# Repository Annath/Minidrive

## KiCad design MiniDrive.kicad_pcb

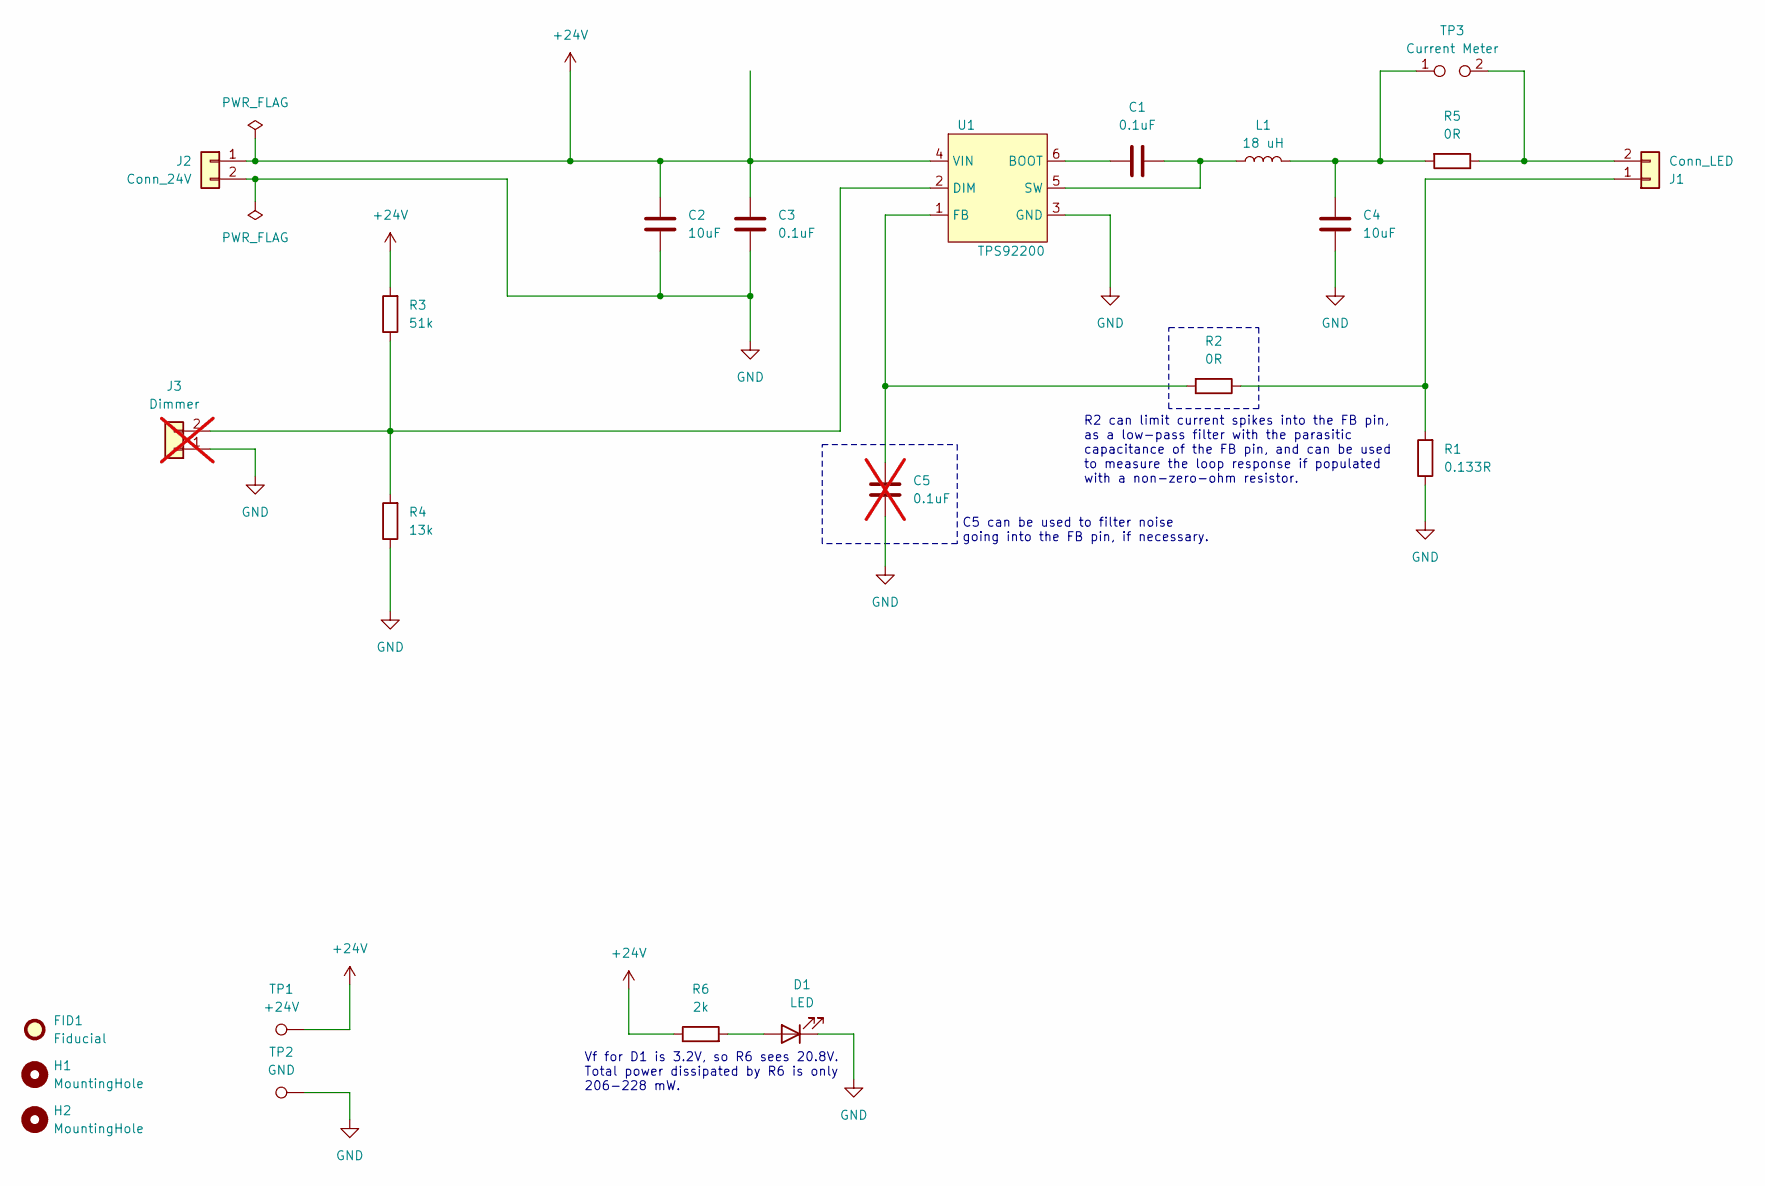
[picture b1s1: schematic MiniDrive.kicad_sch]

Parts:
C1, C3: 0.1uF; C_1210_3225Metric
C2, C4: 10uF; C_1206_3216Metric
C5: 0.1uF; C_0402_1005Metric; not fitted
D1: LED; LED_0603_1608Metric
FID1: Fiducial; Fiducial_0.5mm_Mask1mm
H1, H2: MountingHole; MountingHole_3.2mm_M3
J1: Conn_LED; Molex_Micro-Fit_3.0_43650-0200_1x02_P3.00mm_Horizontal
J2: Conn_24V; Molex_Micro-Fit_3.0_43650-0200_1x02_P3.00mm_Horizontal
J3: Dimmer; JST_PH_B2B-PH-K_1x02_P2.00mm_Vertical; not fitted
L1: 18 uH; L_Wurth_WE-LQS-8040
R1: 0.133R; R_1206_3216Metric
R2, R5: 0R; R_1206_3216Metric
R3: 51k; R_1206_3216Metric
R4: 13k; R_1206_3216Metric
R6: 2k; R_0805_2012Metric
TP1: +24V; TestPoint_THTPad_D1.5mm_Drill0.7mm
TP2: GND; TestPoint_THTPad_D1.5mm_Drill0.7mm
TP3: Current Meter; TestPoint_2Pads_Pitch2.54mm_Drill0.8mm
U1: TPS92200; SOT-23-6

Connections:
+24V: C2.1, C3.1, J2.1, R3.2, R6.1, TP1.1, U1.4 (VIN)
GND: C2.2, C3.2, C4.2, C5.2, D1.1 (K), J2.2, J3.1, R1.1, R4.1, TP2.1, U1.3 (GND)
unnamed: C4.1, L1.2, R5.2, TP3.1
unnamed: D1.2 (A), R6.2
unnamed: J1.1, R1.2, R2.1
unnamed: J1.2, R5.1, TP3.2
unnamed: J3.2, R3.1, R4.2, U1.2 (DIM)
unnamed: C1.2, U1.6 (BOOT)
unnamed: C5.1, R2.2, U1.1 (FB)
unnamed: C1.1, L1.1, U1.5 (SW)

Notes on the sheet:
Vf for D1 is 3.2V, so R6 sees 20.8V. Total power dissipated by R6 is only 206-228 mW.
R2 can limit current spikes into the FB pin, as a low-pass filter with the parasitic capacitance of the FB pin, and can be used to measure the loop response if populated with a non-zero-ohm resistor.
C5 can be used to filter noise going into the FB pin, if necessary.

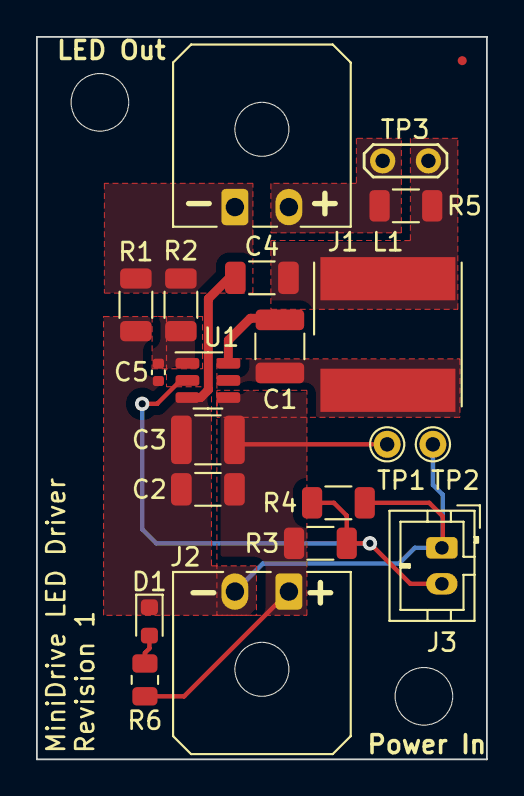
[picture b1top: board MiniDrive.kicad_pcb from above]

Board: 2 copper layers, 25.0 x 40.1 mm, 23 parts (0 on the bottom side), 10 nets.

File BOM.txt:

RefDes  Description                     Mfg         Part #
C1,C3   0.1 uF ceramic capacitor, 1210  Kemet       C1210C104K1RACTM
C2,C4   10 uF ceramic capacitor, 1206   Samsung     CL31B106KBHNNNE
C5*     0.1 uF ceramic capacitor, 0402  Samsung     CL05A104KA5NNNC
D1      Blue LED (3.2V Vf)              Wurth       150060BS55040
J1,J2   2-pin, PCB-mount connector      Molex       43650-0200
J3*     JST PH 2-pin, PTH, vertical     JST         B2B-PH-K-S
L1      18 uH inductor                  Wurth       74404084180
R1      133 mOhms ±1% resistor, 1206    TE Conn     RLC73K2BR133FTDF
R2,R5   0 Ohm jumper/resistor, 1206     Vishay      CRCW12060000Z0EB
R3      51 kOhm ±1% resistor, 1206      Vishay      CRCW120651K0FKEA
R4      13 kOhm ±1% resistor, 1206      Vishay      CRCW120613K0FKEA
R6      2 kOhm ±5% resistor, 0805       Panasonic   ERJ-P06J202V
U1      TPS92200 LED driver             TI          TPS92200D1DDCR

* = do not order, not populated

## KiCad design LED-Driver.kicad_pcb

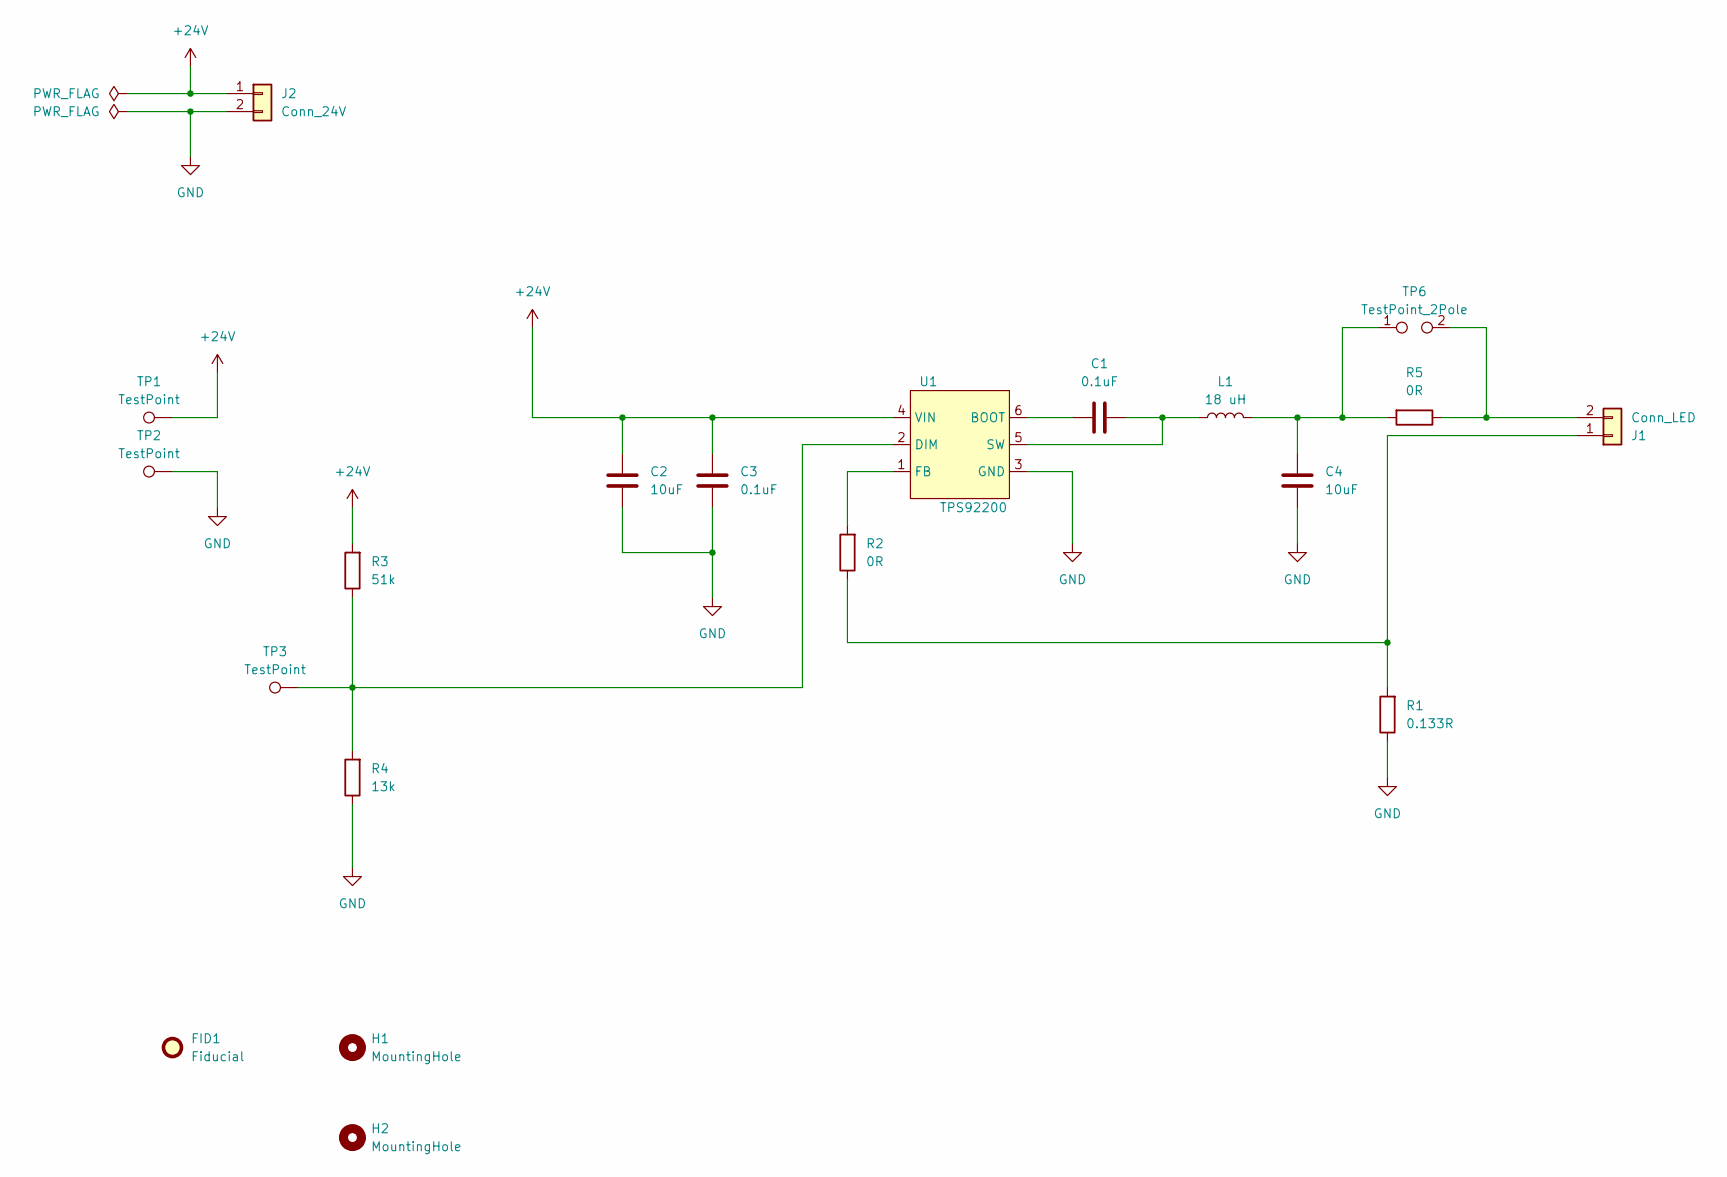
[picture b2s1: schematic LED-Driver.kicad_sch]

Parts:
C1, C3: 0.1uF; C_1210_3225Metric_Pad1.33x2.70mm_HandSolder
C2, C4: 10uF; C_1206_3216Metric_Pad1.33x1.80mm_HandSolder
FID1: Fiducial; Fiducial_0.5mm_Mask1mm
H1, H2: MountingHole; MountingHole_2.7mm_M2.5
J1: Conn_LED; Molex_Micro-Fit_3.0_43650-0200_1x02_P3.00mm_Horizontal
J2: Conn_24V; Molex_Micro-Fit_3.0_43650-0200_1x02_P3.00mm_Horizontal
L1: 18 uH; L_Radial_D8.7mm_P5.00mm_Fastron_07HCP
R1: 0.133R; R_1206_3216Metric_Pad1.30x1.75mm_HandSolder
R2, R5: 0R; R_1206_3216Metric_Pad1.30x1.75mm_HandSolder
R3: 51k; R_1206_3216Metric_Pad1.30x1.75mm_HandSolder
R4: 13k; R_1206_3216Metric_Pad1.30x1.75mm_HandSolder
TP1, TP2, TP3: TestPoint; TestPoint_THTPad_D1.5mm_Drill0.7mm
TP6: TestPoint_2Pole; TestPoint_2Pads_Pitch2.54mm_Drill0.8mm
U1: TPS92200; SOT-23-6_Handsoldering

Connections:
+24V: C2.1, C3.1, J2.1, R3.2, TP1.1, U1.4 (VIN)
GND: C2.2, C3.2, C4.2, J2.2, R1.1, R4.1, TP2.1, U1.3 (GND)
unnamed: C4.1, L1.2, R5.2, TP6.1
unnamed: J1.1, R1.2, R2.1
unnamed: J1.2, R5.1, TP6.2
unnamed: C1.2, U1.6 (BOOT)
unnamed: R3.1, R4.2, TP3.1, U1.2 (DIM)
unnamed: R2.2, U1.1 (FB)
unnamed: C1.1, L1.1, U1.5 (SW)

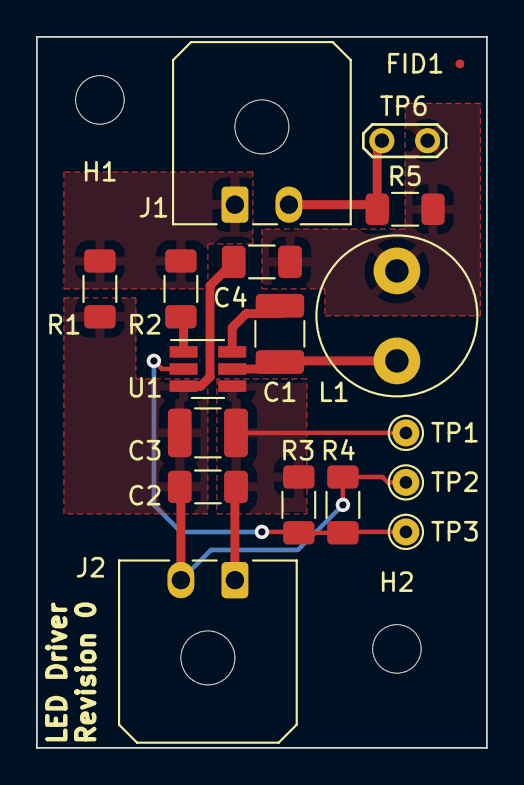
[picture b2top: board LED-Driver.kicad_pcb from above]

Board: 2 copper layers, 25.0 x 39.5 mm, 20 parts (0 on the bottom side), 9 nets.

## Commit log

2023-08-19 Add ignore file
2023-08-19 Add BOM
2023-08-19 Rev 0
2023-08-19 Rename project to MiniDrive
2023-08-19 Minor layout improvements
2023-09-10 BOM updated with correct parts
2023-09-10 Rough draft
2023-09-10 Fixed indentation in BOM
2023-09-10 Add some in-schematic documentation as well as a DNP filter cap for FB
2023-09-10 Fix R2 rotation
2023-09-10 Add C5 to layout
2023-09-10 Change filled zones to solid connections
2023-09-14 Add custom inductor footprint
2023-09-14 Change inductor to SMT
2023-09-14 Update BOM
2023-09-14 Add power LED
2023-09-14 Add off-board dimming connector
2023-09-17 Change mounting holes to M3
2023-09-17 Update 3D model for 8040 inductor
2023-09-23 Clean up schematic and layout
2023-09-23 Revert back to 1206 resistors
2023-09-24 Minor tweaks, remove F1
2024-02-20 Remove unused wire
